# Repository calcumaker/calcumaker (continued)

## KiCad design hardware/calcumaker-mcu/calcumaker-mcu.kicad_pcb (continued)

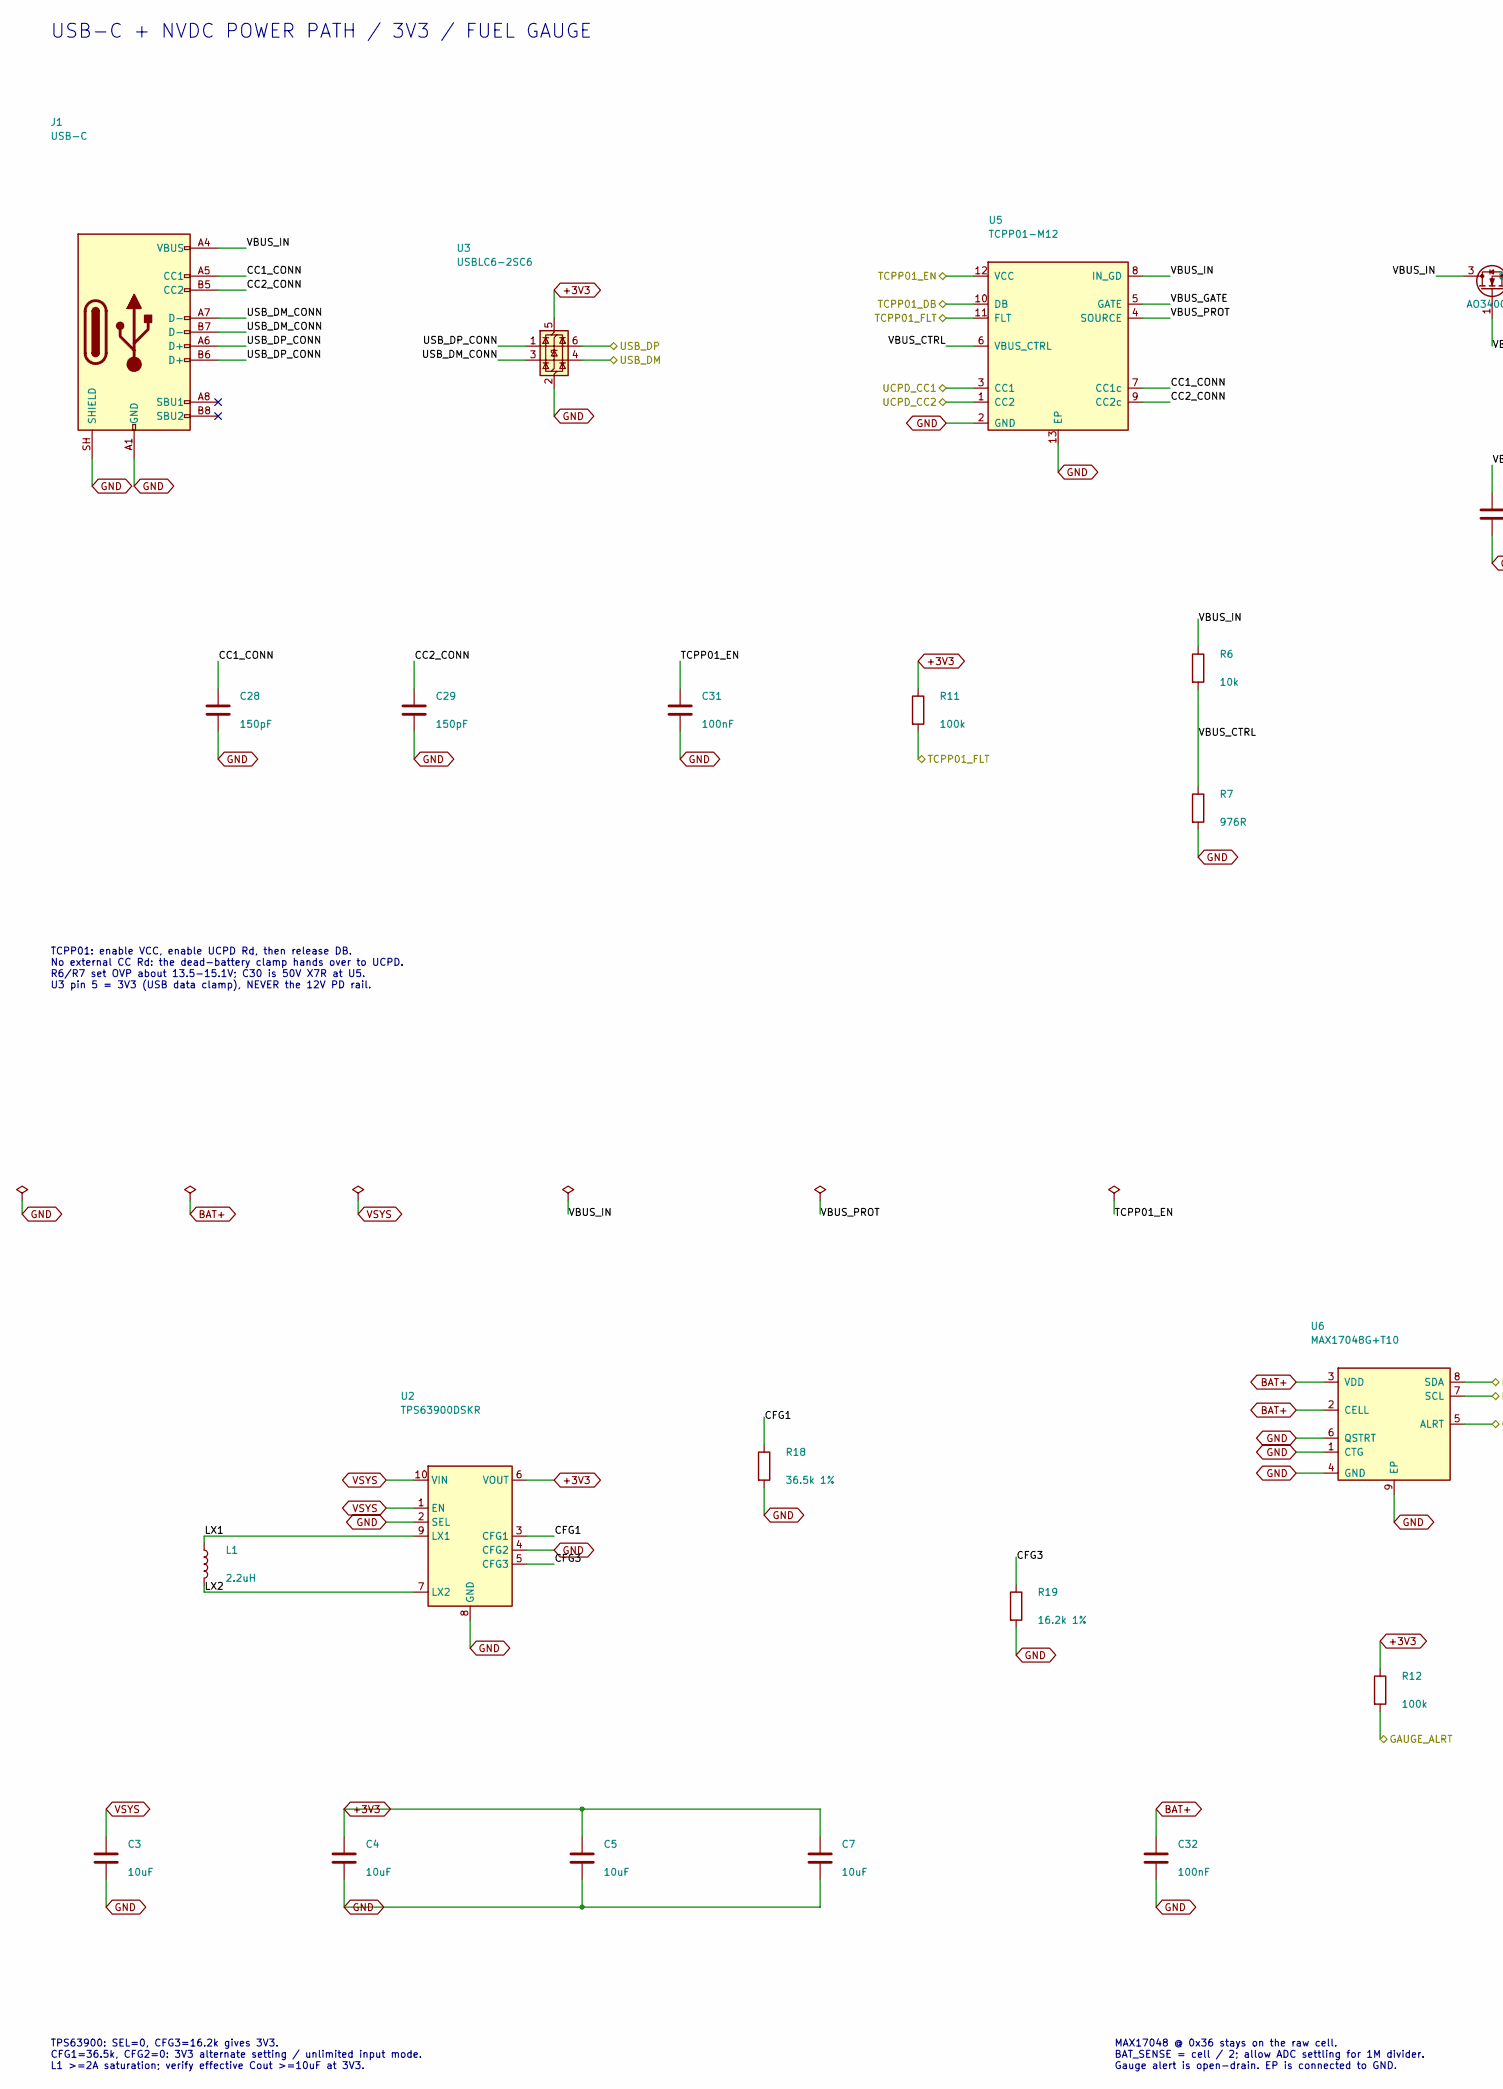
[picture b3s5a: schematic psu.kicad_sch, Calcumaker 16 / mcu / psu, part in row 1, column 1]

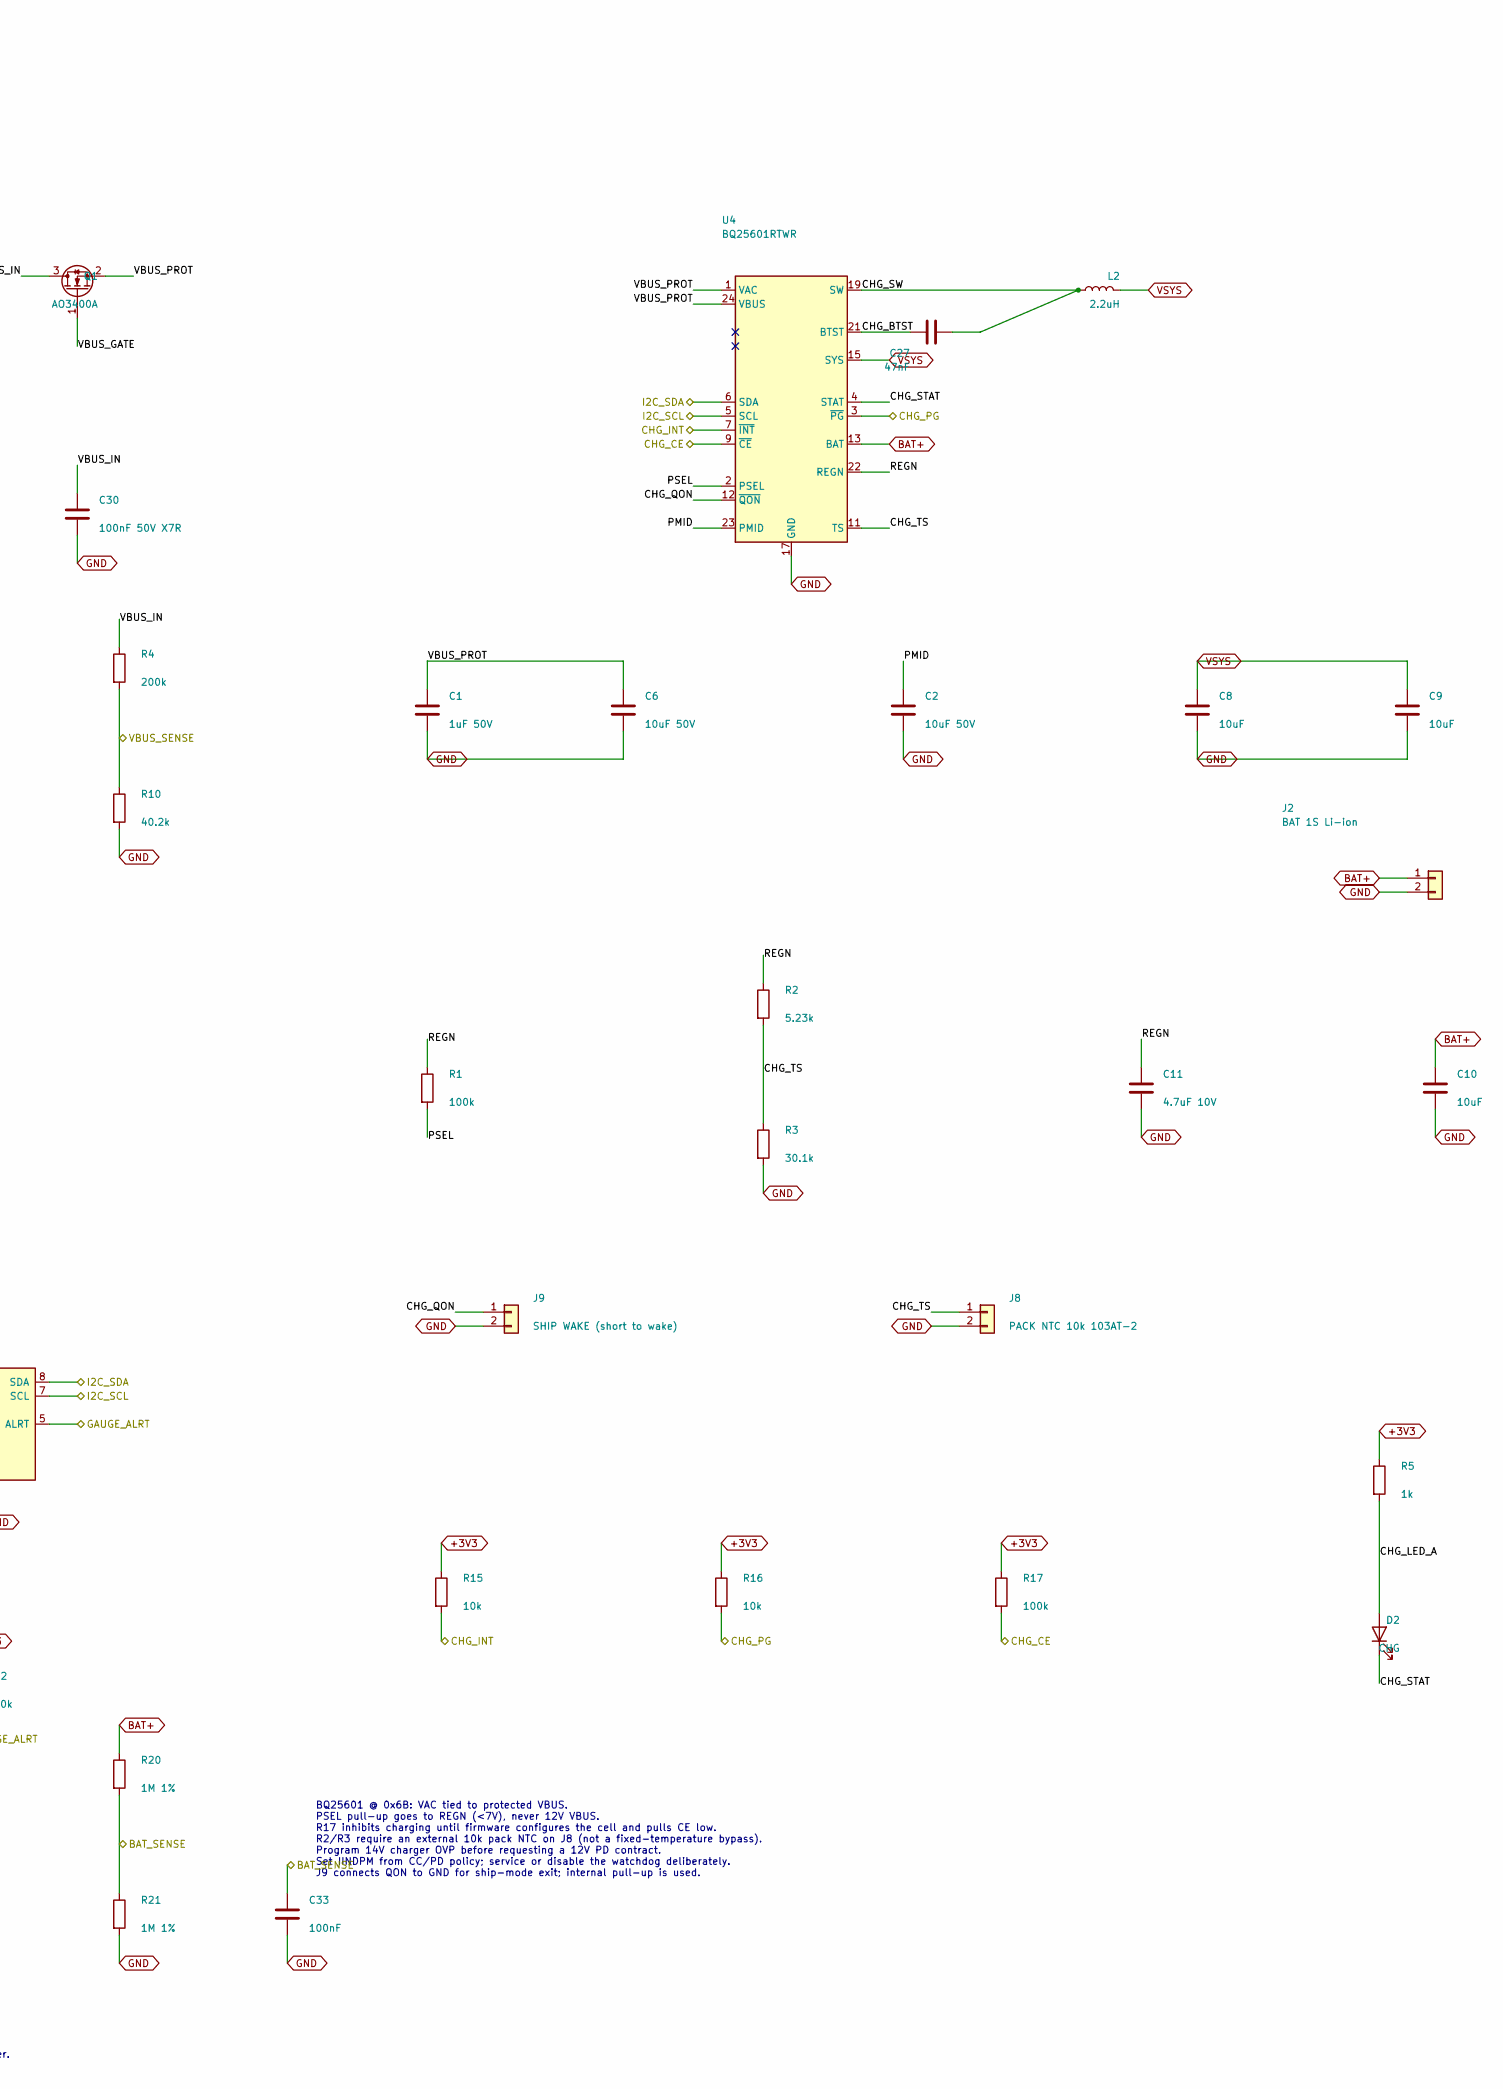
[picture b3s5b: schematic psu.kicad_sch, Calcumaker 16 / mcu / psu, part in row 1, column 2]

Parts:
C1: 1uF 50V; C_0603_1608Metric; MPN CL10A105KB8NNNC; LCSC C15849
C2, C6: 10uF 50V; C_0805_2012Metric; MPN GRM21BR61H106KE43L; LCSC C440198
C3, C4, C5, C7, C8, C9, C10: 10uF; C_0603_1608Metric
C11: 4.7uF 10V; C_0603_1608Metric
C27: 47nF; C_0402_1005Metric
C28, C29: 150pF; C_0402_1005Metric
C30: 100nF 50V X7R; C_0603_1608Metric; MPN CC0603KRX7R9BB104; LCSC C14663
C31, C32: 100nF; C_0402_1005Metric; LCSC C1525
C33: 100nF; C_0402_1005Metric
D2: CHG; LED_0402_1005Metric; LCSC C130719
J1: USB-C; USB_C_Receptacle_GCT_USB4105-xx-A_16P_TopMnt_Horizontal; MPN USB-TYPE-C-019; LCSC C2927039
J2: BAT 1S Li-ion; JST_PH_S2B-PH-K_1x02_P2.00mm_Horizontal; MPN S2B-PH-K-S; LCSC C173752
J8: PACK NTC 10k 103AT-2; JST_PH_S2B-PH-K_1x02_P2.00mm_Horizontal
J9: SHIP WAKE (short to wake); PinHeader_1x02_P2.54mm_Vertical
L1: 2.2uH; L_0805_2012Metric
L2: 2.2uH; L_Changjiang_FNR4020S
Q1: AO3400A; SOT-23; MPN AO3400A; LCSC C20917
R1, R11, R12: 100k; R_0402_1005Metric; LCSC C25741
R2: 5.23k; R_0402_1005Metric
R3: 30.1k; R_0402_1005Metric
R4: 200k; R_0402_1005Metric
R5: 1k; R_0402_1005Metric; LCSC C11702
R6: 10k; R_0402_1005Metric; LCSC C25744
R7: 976R; R_0402_1005Metric
R10: 40.2k; R_0402_1005Metric
R15, R16: 10k; R_0402_1005Metric
R17: 100k; R_0402_1005Metric
R18: 36.5k 1%; R_0402_1005Metric
R19: 16.2k 1%; R_0402_1005Metric
R20, R21: 1M 1%; R_0402_1005Metric
U2: TPS63900DSKR; WSON-10-1EP_2.5x2.5mm_P0.5mm_EP1.2x2mm; MPN TPS63900DSKR; LCSC C1518762
U3: USBLC6-2SC6; SOT-23-6; MPN USBLC6-2SC6; LCSC C2687116
U4: BQ25601RTWR; Texas_RTW_WQFN-24-1EP_4x4mm_P0.5mm_EP2.7x2.7mm_ThermalVias; MPN BQ25601RTWR; LCSC C468236
U5: TCPP01-M12; QFN-12-1EP_3x3mm_P0.5mm_EP1.45x1.45mm_ThermalVias; MPN TCPP01-M12; LCSC C1121848
U6: MAX17048G+T10; TDFN-8-1EP_2x2mm_P0.5mm_EP0.8x1.2mm; MPN MAX17048G+T10; LCSC C2682616

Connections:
+3V3: C4.1, C5.1, C7.1, R5.1, R11.1, R12.1, R15.1, R16.1, R17.1, U2.6 (VOUT), U3.5 (VBUS); also elsewhere on the board
/BAT_SENSE: C33.1, R20.2, R21.1; also elsewhere on the board
/CHG_CE: R17.2, U4.9 (~CE); also elsewhere on the board
/CHG_INT: R15.2, U4.7 (~INT); also elsewhere on the board
/CHG_PG: R16.2, U4.3 (~PG); also elsewhere on the board
/GAUGE_ALRT: R12.2, U6.5 (ALRT); also elsewhere on the board
/I2C_SCL: U4.5 (SCL), U6.7 (SCL); also elsewhere on the board
/I2C_SDA: U4.6 (SDA), U6.8 (SDA); also elsewhere on the board
/PSU/CC1_CONN: C28.1, J1.A5 (CC1), U5.7 (CC1c)
/PSU/CC2_CONN: C29.1, J1.B5 (CC2), U5.9 (CC2c)
/PSU/CFG1: R18.1, U2.3 (CFG1)
/PSU/CFG3: R19.1, U2.5 (CFG3)
/PSU/CHG_BTST: C27.1, U4.21 (BTST)
/PSU/CHG_LED_A: D2.2 (A), R5.2
/PSU/CHG_QON: J9.1, U4.12 (~QON)
/PSU/CHG_STAT: D2.1 (K), U4.4 (STAT)
/PSU/CHG_SW: C27.2, L2.1, U4.19 (SW), U4.20 (SW)
/PSU/CHG_TS: J8.1, R2.2, R3.1, U4.11 (TS)
/PSU/LX1: L1.1, U2.9 (LX1)
/PSU/LX2: L1.2, U2.7 (LX2)
/PSU/PMID: C2.1, U4.23 (PMID)
/PSU/PSEL: R1.2, U4.2 (PSEL)
/PSU/REGN: C11.1, R1.1, R2.1, U4.22 (REGN)
/PSU/USB_DM_CONN: J1.A7 (D-), J1.B7 (D-), U3.3 (I/O2)
/PSU/USB_DP_CONN: J1.A6 (D+), J1.B6 (D+), U3.1 (I/O1)
/PSU/VBUS_CTRL: R6.2, R7.1, U5.6 (VBUS_CTRL)
/PSU/VBUS_GATE: Q1.1 (G), U5.5 (GATE)
/PSU/VBUS_IN: C30.1, J1.A4 (VBUS), J1.A9 (VBUS), J1.B4 (VBUS), J1.B9 (VBUS), Q1.3 (D), R4.1, R6.1, U5.8 (IN_GD)
/PSU/VBUS_PROT: C1.1, C6.1, Q1.2 (S), U4.1 (VAC), U4.24 (VBUS), U5.4 (SOURCE)
/TCPP01_DB: U5.10 (DB); also elsewhere on the board
/TCPP01_EN: C31.1, U5.12 (VCC); also elsewhere on the board
/TCPP01_FLT: R11.2, U5.11 (FLT); also elsewhere on the board
/UCPD_CC1: U5.3 (CC1); also elsewhere on the board
/UCPD_CC2: U5.1 (CC2); also elsewhere on the board
/USB_DM: U3.4 (I/O2); also elsewhere on the board
/USB_DP: U3.6 (I/O1); also elsewhere on the board
/VBUS_SENSE: R4.2, R10.1; also elsewhere on the board
BAT+: C10.1, C32.1, J2.1, R20.1, U4.13 (BAT), U4.14 (BAT), U6.2 (CELL), U6.3 (VDD)
GND: C1.2, C2.2, C3.2, C4.2, C5.2, C6.2, C7.2, C8.2, C9.2, C10.2, C11.2, C28.2, C29.2, C30.2, C31.2, C32.2, C33.2, J1.A1 (GND), J1.A12 (GND), J1.B1 (GND), J1.B12 (GND), J1.SH (SHIELD), J2.2, J8.2, J9.2, R3.2, R7.2, R10.2, R18.2, R19.2, R21.2, U2.2 (SEL), U2.4 (CFG2), U2.8 (GND), U2.11 (GND), U3.2 (GND), U4.17 (GND), U4.18 (GND), U4.25 (GND), U5.2 (GND), U5.13 (EP), U6.1 (CTG), U6.4 (GND), U6.6 (QSTRT), U6.9 (EP); also elsewhere on the board
VSYS: C3.1, C8.1, C9.1, L2.2, U2.1 (EN), U2.10 (VIN), U4.15 (SYS), U4.16 (SYS); also elsewhere on the board

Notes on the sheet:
BQ25601 @ 0x6B: VAC tied to protected VBUS. PSEL pull-up goes to REGN (<7V), never 12V VBUS. R17 inhibits charging until firmware configures the cell and pulls CE low. R2/R3 require an external 10k pack NTC on J8 (not a fixed-temperature bypass). Program 14V charger OVP before requesting a 12V PD c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
MAX17048 @ 0x36 stays on the raw cell. BAT_SENSE = cell / 2; allow ADC settling for 1M divider. Gauge alert is open-drain. EP is connected to GND.
TPS63900: SEL=0, CFG3=16.2k gives 3V3. CFG1=36.5k, CFG2=0: 3V3 alternate setting / unlimited input mode. L1 >=2A saturation; verify effective Cout >=10uF at 3V3.
TCPP01: enable VCC, enable UCPD Rd, then release DB. No external CC Rd: the dead-battery clamp hands over to UCPD. R6/R7 set OVP about 13.5-15.1V; C30 is 50V X7R at U5. U3 pin 5 = 3V3 (USB data clamp), NEVER the 12V PD rail.
USB-C + NVDC POWER PATH / 3V3 / FUEL GAUGE

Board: 2 copper layers, 75 parts (0 on the bottom side), 65 nets, no tracks yet.

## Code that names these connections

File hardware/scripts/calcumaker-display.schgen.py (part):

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DIGIT_FP  = "Display_7Segment:7SegmentLED_LTS6760_LTS6780"  # 0.56" single-digit land

# UNIFIED display-module connector pinout (MUST match mcu J3 + the RGB-matrix J1)
UNIFIED_PINS = {1: "VSYS", 2: "VSYS", 3: "GND", 4: "GND", 5: "+3V3",
                6: "SPI_SCLK", 7: "SPI_MOSI", 8: "SPI_CS",
                9: "DISP_IRQ", 10: "DISP_NRST", 11: "DISP_BOOT", 12: "GND"}
RLCSC = {"10k": "C25744", "100k": "C25741", "732k": "", "4.7k": "C25900"}
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             comments=["Programmer's/technical arbitrary-precision RPN calculator",
                       "Display board: multi-channel 7-seg RPN stack + drivers + interconnect (DRAFT)"])

# segment (FJ5161AH pin name) -> TM1640 SEG line. a..g,dp = SEG1..SEG8 (matches
# firmware seg7 bit order: bit0=a .. bit7=dp -> TM1640 SEG1..SEG8).
SEGMAP = {"A": "SEG1", "B": "SEG2", "C": "SEG3", "D": "SEG4",
          "E": "SEG5", "F": "SEG6", "G": "SEG7", "DP": "SEG8"}
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        wiring += K.net_pin(U, f"GRID{n}", f"GRID{n}")               # right, per digit
    wiring += K.net_pin(U, "VDD", "+5V", kind="glabel")
    wiring += K.net_pin(U, "VSS", "GND", kind="glabel")
    wiring += K.net_pin(U, "SCLK", "DISP_CLK", kind="glabel")         # shared clock
    wiring += K.net_pin(U, "DIN", "DIN", kind="hlabel", shape="input")  # per-row -> sheet pin

    # --- 16 digits (8 across x 2 down) --------------------------------------
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        "  GRID1..16          -  one per digit  (GRID k -> digit k cathode)",
        "  VDD  -> +5V              VSS  -> GND",
        "  SCLK -> DISP_CLK (global net, shared by all 3 rows)",
        "  DIN  -> hierarchical pin (Row1<-DIN1, Row2<-DIN2, Row3<-DIN3 @ root)",
        "",
        "Runs at +5V (VDD + LED) from the MCU-board EN-gated 5V boost.",
        "Digit->GRID is 1:1 sequential; firmware seg7/App is the source of truth.",
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    for pin, net in UNIFIED_PINS.items():
        wiring += K.net_pin(J1, pin, net, kind="glabel")
    C7 = dict(_C("10uF", C0603), x=g(48), y=g(28))
    wiring += K.net_pin(C7, 1, "VSYS", kind="glabel")     # bulk on the incoming VSYS
    wiring += K.net_pin(C7, 2, "GND", kind="glabel")
    comps = [(J1, [(path, "J1")]), (C7, [(path, "C7")])]
    note = (20.0, 120.0, K.note_block(
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        "0.5mm 12-pos FFC to the MCU board. SAME connector + pinout as the RGB-",
        "matrix board's J1 and mcu J3 -> the display modules are INTERCHANGEABLE.",
        "",
        K.pin_table([(1, "VSYS"), (2, "VSYS"), (3, "GND"), (4, "GND"), (5, "+3V3"),
                     (6, "SPI_SCLK"), (7, "SPI_MOSI"), (8, "SPI_CS"), (9, "DISP_IRQ"),
                     (10, "DISP_NRST (G0 NRST)"), (11, "DISP_BOOT (G0 BOOT0)"),
                     (12, "GND")]),
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    w += K.net_pin(U4, 4, "+3V3", kind="glabel")          # VDD
    w += K.net_pin(U4, 5, "GND", kind="glabel")           # VSS
    w += K.net_pin(U4, 33, "GND", kind="glabel")          # VSS/EP
    w += K.net_pin(U4, 6, "DISP_NRST", kind="glabel")     # PF2/NRST
    w += K.net_pin(U4, 7, "DISP_IRQ", kind="glabel")      # PA0 -> IRQ out
    w += K.net_pin(U4, 11, "SPI_CS", kind="glabel")       # PA4  SPI1 NSS
    w += K.net_pin(U4, 12, "SPI_SCLK", kind="glabel")     # PA5  SPI1 SCK
    w += K.net_pin(U4, 14, "SPI_MOSI", kind="glabel")     # PA7  SPI1 MOSI
    w += K.net_pin(U4, 24, "SWDIO", kind="label")         # PA13
    w += K.net_pin(U4, 25, "SWCLK", kind="label")         # PA14
    w += K.net_pin(U4, 15, "CLK_3V3", kind="glabel")      # PB0 -> shifter -> DISP_CLK
    w += K.net_pin(U4, 16, "DIN1_3V3", kind="glabel")     # PB1 -> DIN1
    w += K.net_pin(U4, 17, "DIN2_3V3", kind="glabel")     # PB2 -> DIN2
    w += K.net_pin(U4, 27, "DIN3_3V3", kind="glabel")     # PB3 -> DIN3
    w += K.net_pin(U4, 30, "OLED_SCL", kind="glabel")     # PB6 I2C1 SCL
    w += K.net_pin(U4, 31, "OLED_SDA", kind="glabel")     # PB7 I2C1 SDA

    # decoupling + reset
    for i, (ref, val, fp) in enumerate([("C8", "100nF", C0402), ("C9", "100nF", C0402),
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        w += K.net_pin(c, 1, "+3V3", kind="glabel")
        w += K.net_pin(c, 2, "GND", kind="glabel")
    C12 = one(dict(C("C12", "100nF"), x=g(30), y=g(66)), "C12")       # NRST cap
    w += K.net_pin(C12, 1, "DISP_NRST", kind="glabel")
    w += K.net_pin(C12, 2, "GND", kind="glabel")
    R1 = one(dict(R("R1", "10k"), x=g(36), y=g(66)), "R1")            # BOOT0/DISP_BOOT pulldown
    w += K.net_pin(R1, 1, "DISP_BOOT", kind="glabel")
    w += K.net_pin(R1, 2, "GND", kind="glabel")

    # SWD Tag-Connect
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                  value="SWD TC2030-NL", fp=SWD_FP, x=g(60), y=g(44)), "J3")
    w += K.net_pin(J3, 1, "+3V3", kind="glabel")
    w += K.net_pin(J3, 2, "SWDIO", kind="label")
    w += K.net_pin(J3, 3, "DISP_NRST", kind="glabel")
    w += K.net_pin(J3, 4, "SWCLK", kind="label")
    w += K.net_pin(J3, 5, "GND", kind="glabel")

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        "MODULE MCU (WIRED)  -  U4 STM32G031K8U6 (C432207, UFQFPN-32)",
        "SPI-slave frame receiver -> renders 'display intent' to the 3 TM1640s.",
        "POWER  VDD(4)->+3V3 (C8/C9 100nF + C11 4.7uF); VSS(5,33)->GND.",
        "RESET  NRST=PF2(6)->DISP_NRST + C12 100nF.  BOOT0: R1 10k on DISP_BOOT;",
        "       route to the G031 BOOT0/option-byte at layout (UART-boot entry).",
        "LINK   SPI1 PA5/PA7/PA4 <- SPI_SCLK/MOSI/CS;  PA0 -> DISP_IRQ.",
        "DRIVE  PB0-3 -> CLK_3V3 + DIN1/2/3_3V3 (3V3) -> DispPower shifters -> 5V",
        "       to the TM1640s (Row1-3). CLOCK internal HSI.",
        "OLED   PB6/PB7 = I2C1 SCL/SDA -> AuxDisplay J2.  PROG  J3 SWD Tag-Connect."))
    return dict(uuid=MCU_SH, file="disp_mcu.kicad_sch", page="8",
                title="Module MCU (STM32G031K8U6, SPI-slave) — wired",
                comps=comps, wiring=w, notes=[note], _dir=PROJ_DIR)
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    U5 = one(dict(lib_id="Converter_DCDC:TPS61022", value="TPS61022RWUR", fp=BOOST_FP,
                  lcsc="C915088", mpn="TPS61022RWUR", mfr="Texas Instruments",
                  x=g(30), y=g(44)), "U5")
    w += K.net_pin(U5, 7, "VSYS", kind="glabel")          # VIN
    w += K.net_pin(U5, 2, "SW", kind="label")             # SW node (to L1)
    w += K.net_pin(U5, 3, "+5V", kind="glabel")           # VOUT
    w += K.net_pin(U5, 4, "FB", kind="label")             # feedback
    w += K.net_pin(U5, 5, "VSYS", kind="glabel")          # EN -> always on (gate off = a GPIO later)
    w += K.net_pin(U5, 6, "GND", kind="glabel")           # MODE -> GND (forced PWM)
    w += K.net_pin(U5, 1, "GND", kind="glabel")           # GND
    L1 = one(dict(lib_id="Device:L", value="1uH", fp=L2016, lcsc="C5832342",
                  mpn="FTC201610S1R0MBCA", mfr="Sunlord", x=g(18), y=g(40)), "L1")
    w += K.net_pin(L1, 1, "VSYS", kind="glabel")
    w += K.net_pin(L1, 2, "SW", kind="label")
    C13 = one(dict(C("C13", "10uF", C0603), x=g(10), y=g(50)), "C13")   # Cin
    w += K.net_pin(C13, 1, "VSYS", kind="glabel")
    w += K.net_pin(C13, 2, "GND", kind="glabel")
    for i, ref in enumerate(("C14", "C15")):                            # Cout 2x22uF
        c = one(dict(C(ref, "22uF", C0603), x=g(46 + i * 5), y=g(50)), ref)
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        "LOCAL 5V RAIL + LEVEL SHIFT (WIRED)  -  moved off the MCU board.",
        "5V BOOST  U5 TPS61022 (C915088): VIN<-VSYS, L1 1uH (VSYS->SW), Cin C13",
        "  10uF, Cout C14/C15 2x22uF; FB R2 732k / R3 100k -> +5V (Vref 0.6V).",
        "  EN->VSYS (always on; tie to a G031 GPIO to gate off in deep sleep).",
        "SHIFT  U6-U9 74HCT1G125 @ +5V (VIH=2V accepts 3V3): A <- G031 CLK/DIN1/2/3",
        "  (3V3), Y -> DISP_CLK + DIN1/2/3 (5V) to the TM1640s. /OE=GND; C16-19",
        "  decouple. *** VERIFY the 74HCT1G125GW package (SOT-353 vs the SOT-23-5",
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# ============================ root sheet ====================================
def build_root_strings():
    # 3 reused row instances + interconnect + aux, with per-row DIN routed to
    # DIN1/2/3 global labels.
    sym = ""
    wiring = ""
    for i, (uuid, name) in enumerate([(R1, "Row1"), (R2, "Row2"), (R3, "Row3")]):
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        "Calcumaker 16 — Display (MULTI-CHANNEL). Row1/2/3 are three instances "
        "of ONE reusable sheet (display_row.kicad_sch). Shared bus is carried on "
        "global nets +5V / GND / DISP_CLK; each row's serial data DIN is a "
        "hierarchical pin fed by DIN1/DIN2/DIN3 from the interconnect. Top row "
        "(Row3 / U3 / DS33-48) is optional -> 2- or 3-row build.", 20.0, 105.0)
    pro_sheets = [[R1, "Row1"], [R2, "Row2"], [R3, "Row3"],
                  [IC, "Interconnect"], [AX, "AuxDisplay"],
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
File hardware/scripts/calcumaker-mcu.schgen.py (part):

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        dict(ref="J3", lib_id="Connector_Generic:Conn_01x12", value="TO DISPLAY (unified SPI FFC)",
             fp="Connector_FFC-FPC:Hirose_FH12-12S-0.5SH_1x12-1MP_P0.50mm_Horizontal",
             lcsc="C262661", mpn="AFC01-S12FCA-00", mfr="JUSHUO"),
        # VSYS outlet -> the RGB-matrix module's LED inlet (its own 2-pin JST).
        dict(ref="J7", lib_id="Connector_Generic:Conn_01x02", value="VSYS -> matrix LED pwr",
             fp="Connector_JST:JST_PH_S2B-PH-K_1x02_P2.00mm_Horizontal",
             lcsc="C173752", mpn="S2B-PH-K-S", mfr="JST"),
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        "",
        "PIN MAP  (verified vs the ST CubeMX pin DB for LQFP-64)",
        "  OCTOSPI1 -> U7      OCTOSPIM Port 1; IO0-3 forced, 1 pin each",
        "    CLK  PB10 AF10 p29      IO0  PB1  AF10 p27",
        "    NCS  PA4  AF3  p20      IO1  PB0  AF10 p26",
        "                            IO2  PA7  AF10 p23",
        "                            IO3  PA6  AF10 p22",
        "  SPI1 -> display J3  (PA6/PA7 are QSPI now; the FFC has no MISO)",
        "    SCK  PA5  AF5  p21      MOSI PB5  AF5  p57",
        "    CS   PA8       p41      (plain GPIO -- MOVED off PA15, now UCPD1_CC1)",
        "  UCPD1  -> USB-C CC   CC1 PA15 p50 / CC2 PB15 p63   (dedicated analog,",
        "                       NO AF alt -- this is why SPI1 CS had to move.",
        "                       Rd is INTERNAL: no 5.1k parts.  DBCC1/DBCC2 unused,",
        "                       so PB5 stays SPI1 MOSI.)",
        "  USART2 -> keyboard   TX PA2 p16 / RX PA3 p17   AF7",
        "  I2C1   -> keyboard + CHARGER   SCL PB6 p58 / SDA PB7 p59 AF4",
        "                       (shared bus; BQ25601 = 0x6B, no addr clash)",
        "",
        "ON THIS SHEET  (Clock / Programming / DisplayIF merged in here)",
        "  SWD   PA13/PA14 (+ PB3 SWO)      -> J4 Tag-Connect (+ NRST)",
        "  LSE   PC14/PC15 OSC32            -> Y1 + C24/C25",
        "  DISP  SPI1 + DISP_IRQ/NRST/BOOT  -> J3 FFC ; J7 VSYS outlet",
        "",
        "OFF-SHEET",
        "  USB   PA11/PA12                     -> PSU ESD (U3)",
        "  CC    PA15/PB15 (UCPD1)             -> PSU ESD (U5) -> USB-C CC1/CC2",
        "  CHG   I2C1 + CHG_INT/CHG_PG/CHG_CE  -> PSU charger U4",
        "  KBD   I2C1+USART2+KB_IRQ/NRST/BOOT0 -> KeyboardIF J5/J6",
        "  QSPI  OCTOSPI1 CLK/NCS/IO0-3        -> QSPIFlash U7",
        "",
        "KB_IRQ must land on a WKUP pin (keypress wake from Stop) -- still open.",
        "",
        "---- J3  UNIFIED DISPLAY-MODULE FFC  (was the DisplayIF sheet) --------",
        "0.5mm 12-pos FFC (AFC01-S12FCA-00, C262661). SAME pinout on BOTH display",
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        "7-seg / RP2040 on the matrix) is the SPI slave + renders locally; 5V and",
        "any level-shifting are generated ON the module now.",
        "",
        K.pin_table([(1, "VSYS"), (2, "VSYS"), (3, "GND"), (4, "GND"), (5, "+3V3"),
                     (6, "SPI_SCLK"), (7, "SPI_MOSI"), (8, "SPI_CS"), (9, "DISP_IRQ"),
                     (10, "DISP_NRST"), (11, "DISP_BOOT"), (12, "GND")]),
        "",
        "J7 = 2-pin JST-PH VSYS outlet -> the RGB-matrix module's LED inlet (J2):",
        "the matrix pulls amps for 2304 LEDs, so its LED current takes this direct",
        "lead, NOT the signal FFC (the 7-seg module boosts from VSYS on the FFC).",
        "CABLE (non-BOM): GCT FFC05-TIN 05-12-A-<len>-A-4-06-4-T (DigiKey; len TBD).",
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        "---- J4  SWD PROGRAMMING  (was the Programming sheet) ----------------",
        "Tag-Connect TC2030-NL (no-legs pogo pad). Bare land, no part mounted.",
        "",
        K.pin_table([(1, "+3V3 (VTref)"), (2, "SWDIO (PA13)"), (3, "NRST"),
                     (4, "SWCLK (PA14)"), (5, "GND"), (6, "SWO (PB3, opt)")], cols=1),
        "",
        "---- Y1  LSE 32.768 kHz  (was the Clock sheet) -----------------------",
        "Q13FC13500004, LCSC C32346.  Y1.1 -> OSC32_IN (PC14)",
        "                             Y1.2 -> OSC32_OUT (PC15)",
        "  C24 / C25 -> LSE load caps to GND   (12pF shown)",
        "Load caps: CL match = 2*(CL - Cstray); trim with the RTC SMOOTHCALIB.",
        "Drives the RTC for sleep timing.")))
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        #      and closes the CC switches, handing CC over to UCPD.  This is what
        #      closes the old "dead-battery Rd" risk (was Open Question 8).
        #   2. CC SHORT-TO-VBUS OVP (6.0V clamp).  A defective cable/source putting
        #      20V on CC would otherwise destroy PA15/PB15 -- a USBLC6 is an ESD
        #      clamp (ns transients), NOT sustained-overvoltage protection.
        # Plus IEC61000-4-2 level 4 ESD on CC, and adjustable VBUS OVP via an
        # external N-FET it gate-drives.  Sourced by the user: 300 pcs on JLCPCB.
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        dict(ref="U3", lib_id="Power_Protection:USBLC6-2SC6", value="USBLC6-2SC6",
             fp=SOT236, lcsc="C2687116", mpn="USBLC6-2SC6", mfr="STMicroelectronics"),
        # -- USB-C CC -> TCPP01 (connector side CC1c/CC2c, 22V tolerant) -> MCU side
        # CC1/CC2 -> the U575's UCPD1 (CC1=PA15, CC2=PB15; dedicated analog pins, NO
        # AF alternative -- which is why the display SPI1 CS moved off PA15 to PA8).
        # There are NO 5.1k Rd resistors: in the run state UCPD generates Rd
        # INTERNALLY (CcPull::Sink).  It is either/or -- an external 5.1k in parallel
        # with the internal Rd = 2.55k, and the source would misread us as an audio
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        # (UCPD_SR.TYPEC_VSTATE_CC: LOWEST=detached LOW=500mA HIGH=1.5A HIGHEST=3.0A);
        # fw reads it and writes IINDPM over I2C.  UCPD also carries the BMC PHY, so
        # real USB-PD later is FIRMWARE-ONLY -- no respin.
        #   DB/ is a plain 3V3 GPIO (NOT the UCPD DBCC1/DBCC2 pins) -- so PB5 stays
        #   SPI1 MOSI and DBCC1/DBCC2 remain unused.  Datasheet 6.4.
        R("R11", "100k"),                                # FLT/ pull-up (open-drain)
        # VBUS OVP threshold: VBUS_CTRL trips at Vovp = 1.20 (min) / 1.25 (typ) /
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        "    !! BELOW a legal 12V source -> nuisance trips on a good charger.",
        "  VBUS SENSE:  J1 VBUS -> R4 200k -> VBUS_SENSE (ADC) -> R10 40.2k -> GND",
        "    (not needed at 5V; a PD policy engine REQUIRES it -> keeps PD fw-only)",
        "  CC:  J1 CC1 -> CC1c(7) ... CC1(3) -> PA15 (UCPD1_CC1)   [+C28 150pF]",
        "       J1 CC2 -> CC2c(9) ... CC2(1) -> PB15 (UCPD1_CC2)   [+C29 150pF]",
        "    connector side is 22V tolerant; U5 clamps CC at 6.0V -> a CC short to",
        "    VBUS can no longer destroy the MCU's CC pins.",
        "  CONTROL:  VCC(12) <- TCPP01_EN GPIO (+C31 100nF)  -- powering VCC from a",
        "    GPIO gives NULL quiescent current when unplugged (datasheet 5).",
        "            DB/(10)  <- TCPP01_DB  GPIO   (plain 3V3 GPIO, NOT UCPD DBCC!",
        "                                          so PB5 stays SPI1 MOSI)",
        "            FLT/(11) -> TCPP01_FLT GPIO   open-drain, + R11 100k pull-up",
        "            GND(2) + EP(13) -> GND   <-- EP IS A REAL GROUND RETURN, not just",
        "                                         thermal.  It is a VISIBLE pin: WIRE IT.",
        "",
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# wake line (keyboard -> MCU) and reset/boot for reflashing the keyboard MCU.
# J5 = Hirose DF40 2x6 (12-pin) 0.4mm RECEPTACLE (DF40B-12DS, LCSC C3641147); the
# keyboard board carries the mating header (DF40C-12DP C6224952). Grown 10 -> 12
# pins to carry VSYS + a dedicated GND up to the keyboard for its per-key RGB
# lighting. (DF40C-12DS isn't LCSC-stocked, so the receptacle is DF40B-12DS --
# same 1.5mm stack: on DF40 the receptacle SUFFIX sets the height [none=1.5mm,
# (2.0)=2.0mm], not the B/C letter, and the DF40C plug is the common header.)
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        "PLACED, not wired.  The keyboard end (MainIF) mirrors both connectors.",
        "",
        "J5 DF40 (12-pin):",
        K.pin_table([(1, "+3V3"), (2, "GND"), (3, "SDA"), (4, "SCL"), (5, "UART_TX"),
                     (6, "UART_RX"), (7, "KB_IRQ"), (8, "KB_NRST"), (9, "KB_BOOT0"),
                     (10, "GND"), (11, "VSYS"), (12, "GND")]),
        "J6 FFC (16-pin: VSYS x2, GND x3 for LED current + 2 spare):",
        K.pin_table([(1, "+3V3"), (2, "GND"), (3, "SDA"), (4, "SCL"), (5, "UART_TX"),
                     (6, "UART_RX"), (7, "KB_IRQ"), (8, "KB_NRST"), (9, "KB_BOOT0"),
                     (10, "GND"), (11, "VSYS"), (12, "VSYS"), (13, "GND"), (14, "GND"),
                     (15, "NC"), (16, "NC")]),
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        "QSPI FLASH  -  U7  W25Q32JVSSIQ  (LCSC C179173)",
        "4MB (32Mbit) quad-SPI NOR, SOIC-8, 2.7-3.6V, on the STM32U575 OCTOSPI1.",
        "",
        K.pin_table([("1", "CS#         <-  NCS     PA4   AF3    p20  (+R9 10k)"),
                     ("6", "CLK         <-  CLK     PB10  AF10   p29"),
                     ("5", "IO0 / DI    <-> IO0     PB1   AF10   p27"),
                     ("2", "IO1 / DO    <-> IO1     PB0   AF10   p26"),
                     ("3", "IO2 / WP#   <-> IO2     PA7   AF10   p23"),
                     ("7", "IO3 / HOLD# <-> IO3     PA6   AF10   p22"),
                     ("8", "VCC = +3V3   (C26 100nF at pin 8)"),
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
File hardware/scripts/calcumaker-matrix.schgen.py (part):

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**data chain** (768 LEDs) driven by one RP2040 PIO line via the quad level shifter.

**Power.** LED current (amps at brightness) does NOT cross the signal FFC: the
board takes a dedicated 2-pin VSYS inlet (J2) from the MCU-board PSU, gated by a
high-side load switch (LED_EN off in sleep). Firmware MUST cap total brightness.

This is DATA; the engine is scripts/kschgen.py. Verify each lib_id/footprint
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CLCSC = {"100nF": "C1525", "1uF": "C29266", "10uF": "C15850", "22uF": "C45783", "15pF": ""}

# ---- UNIFIED display-module connector pinout (MUST match mcu J3 + 7-seg J1) --
UNIFIED_PINS = {1: "VSYS", 2: "VSYS", 3: "GND", 4: "GND", 5: "+3V3",
                6: "SPI_SCLK", 7: "SPI_MOSI", 8: "SPI_CS",
                9: "DISP_IRQ", 10: "DISP_NRST", 11: "DISP_BOOT", 12: "GND"}

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                   x=g(8 + cc * 6), y=g(10 + rr * 6))
        # ref: global cluster index gc = r*12 + c ; 64 LEDs per cluster
        comps.append((led, pr(lambda r, c, jj=j: f"D{(r * NCLUST + c) * PER_CLUSTER + jj}")))
        wiring += K.net_pin(led, "VDD", "VLED", kind="glabel")
        wiring += K.net_pin(led, "VSS", "GND", kind="glabel")
        if j == 1:
            wiring += K.net_pin(led, "DIN", "DIN", kind="hlabel", shape="input")
        else:
            wiring += K.net_pin(led, "DIN", f"CN{j}", kind="label")
        if j == PER_CLUSTER:
            wiring += K.net_pin(led, "DOUT", "DOUT", kind="hlabel", shape="output")
        else:
            wiring += K.net_pin(led, "DOUT", f"CN{j + 1}", kind="label")

    note = (g(4), g(66), K.note_block(
        "REUSABLE 8x8 LED CLUSTER  (leaf of the nested design)",
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        "Refs D1..D2304: cluster gc = r*12+c  ->  D(64*gc+1) .. D(64*gc+64).",
        "",
        "64x XL-1010RGBC-2812B-S (C51900942, 1x1mm WS2812/SK6812, 3.5-5.5V):",
        "  DIN -> LED1 -> ... -> LED64 -> DOUT  (serpentine; DIN/DOUT = hier pins,",
        "         chained cluster-to-cluster in led_row, row-to-row at the root)",
        "  VDD -> VLED (gated LED rail);  VSS -> GND",
        "",
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        # DOUT side: cluster 11 = row DOUT (hier); else RC{c+1}
        wiring += K.w_wire(cx + cw, opy, cx + cw + g(2), opy)
        if c == NCLUST - 1:
            wiring += K.w_hlabel("DOUT", cx + cw + g(2), opy, 0, shape="output")
        else:
            wiring += K.w_label(f"RC{c + 1}", cx + cw + g(2), opy, 0)
    note = K.text_note(K.note_block(
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    for n, net in [(52, "QSPI_SCLK"), (53, "QSPI_SD0"), (55, "QSPI_SD1"),
                   (54, "QSPI_SD2"), (51, "QSPI_SD3"), (56, "QSPI_CS")]:
        w += K.net_pin(U1, n, net, kind="glabel")
    w += K.net_pin(U1, 47, "USB_DP", kind="glabel")
    w += K.net_pin(U1, 46, "USB_DM", kind="glabel")
    w += K.net_pin(U1, 26, "DISP_NRST", kind="glabel")    # RUN <- reset from U575
    w += K.net_pin(U1, 24, "SWCLK", kind="glabel")
    w += K.net_pin(U1, 25, "SWDIO", kind="glabel")
    # peripheral GPIOs (by pin number)
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    w += K.net_pin(U3, "VBUS", "VBUS", kind="glabel")
    w += K.net_pin(U3, "GND", "GND", kind="glabel")
    R2 = one(dict(R("R2", "27"), x=g(40), y=g(72)), "R2")
    w += K.net_pin(R2, 1, "USB_DP", kind="glabel")
    w += K.net_pin(R2, 2, "USB_DP_C", kind="label")
    R3 = one(dict(R("R3", "27"), x=g(40), y=g(78)), "R3")
    w += K.net_pin(R3, 1, "USB_DM", kind="glabel")
    w += K.net_pin(R3, 2, "USB_DM_C", kind="label")
    J4 = one(dict(lib_id="Connector:USB_C_Receptacle_USB2.0_16P", value="USB-C (BOOTSEL)",
                  fp=USBC_FP, lcsc="C2927039", mpn="USB-TYPE-C-019", mfr="GCT",
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    J2 = one(dict(lib_id="Connector_Generic:Conn_01x02", value="VSYS IN (LED pwr)",
                  fp=JST2_FP, lcsc="C173752", mpn="S2B-PH-K-S", mfr="JST",
                  x=g(8), y=g(12)), "J2")
    w += K.net_pin(J2, 1, "VSYS", kind="glabel")
    w += K.net_pin(J2, 2, "GND", kind="glabel")

    # High-side P-FET: VSYS -> VLED, gate = QG (R5 pull-up to VSYS = OFF default)
    Q1 = one(dict(lib_id="Transistor_FET:Q_PMOS_GSD", value="AO3401A", fp=SOT23,
                  lcsc="C15127", mpn="AO3401A", mfr="AOS", x=g(26), y=g(16)), "Q1")
    w += K.net_pin(Q1, "S", "VSYS", kind="glabel")
    w += K.net_pin(Q1, "D", "VLED", kind="glabel")
    w += K.net_pin(Q1, "G", "QG", kind="label")
    R5 = one(dict(R("R5", "100k"), x=g(26), y=g(6)), "R5")
    w += K.net_pin(R5, 1, "VSYS", kind="glabel")
    w += K.net_pin(R5, 2, "QG", kind="label")
    # N-FET pulls QG low when LED_EN is high (R7 pulldown = OFF at boot/sleep)
    Q2 = one(dict(lib_id="Transistor_FET:Q_NMOS_GSD", value="2N7002", fp=SOT23,
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    w += K.net_pin(Q2, "S", "GND", kind="glabel")
    w += K.net_pin(Q2, "G", "QEN", kind="label")
    R6 = one(dict(R("R6", "10k"), x=g(40), y=g(26)), "R6")
    w += K.net_pin(R6, 1, "LED_EN", kind="glabel")
    w += K.net_pin(R6, 2, "QEN", kind="label")
    R7 = one(dict(R("R7", "100k"), x=g(48), y=g(26)), "R7")
    w += K.net_pin(R7, 1, "QEN", kind="label")
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    for i, (ref, val, fp) in enumerate([("C13", "22uF", C0603), ("C14", "22uF", C0603),
                                        ("C15", "100nF", C0402)]):
        c = one(dict(C(ref, val, fp), x=g(56 + i * 5), y=g(12)), ref)
        w += K.net_pin(c, 1, "VLED", kind="glabel")
        w += K.net_pin(c, 2, "GND", kind="glabel")

    # 3x single-gate shifter: A <- LED_DATAk (RP2040 3V3), Y -> CHk_DATA (VLED);
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        U = one(dict(lib_id="74xGxx:74LVC1G125", value="74LVC1G125", fp=SOT235,
                     lcsc="C23654", mpn="SN74LVC1G125DBVR", mfr="Texas Instruments",
                     x=g(10 + (k - 1) * 18), y=g(44)), f"U{3 + k}")
        w += K.net_pin(U, 5, "VLED", kind="glabel")            # VCC
        w += K.net_pin(U, 3, "GND", kind="glabel")             # GND
        w += K.net_pin(U, 1, "GND", kind="glabel")             # /OE low = enabled
        w += K.net_pin(U, 2, f"LED_DATA{k}", kind="glabel")    # A  <- RP2040 (3V3)
        w += K.net_pin(U, 4, f"CH{k}_DATA", kind="glabel")     # Y  -> chain k
        cc = one(dict(C(f"C{15 + k}", "100nF"), x=g(10 + (k - 1) * 18), y=g(54)), f"C{15 + k}")
        w += K.net_pin(cc, 1, "VLED", kind="glabel")
        w += K.net_pin(cc, 2, "GND", kind="glabel")

    note = (g(4), g(64), K.note_block(
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        "no display-specific lines). Distinct pinout from the old CLK/DIN display",
        "FFC and from the 16-pin keyboard link (can't cross-plug).",
        "",
        K.pin_table([(1, "VSYS"), (2, "VSYS"), (3, "GND"), (4, "GND"), (5, "+3V3"),
                     (6, "SPI_SCLK"), (7, "SPI_MOSI"), (8, "SPI_CS"), (9, "DISP_IRQ"),
                     (10, "DISP_NRST (RP2040 RUN)"), (11, "DISP_BOOT (RP2040 BOOTSEL)"),
                     (12, "GND")]),
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        "the unified connector -- the main MCU sends OLED content inside the SPI",
        "display-intent stream. Add 4.7k pull-ups (DNP with the module).",
        "",
        K.pin_table([(1, "VCC <- +3V3"), (2, "GND"), (3, "SCL <- OLED_SCL"),
                     (4, "SDA <- OLED_SDA")], cols=1),
        "",
        "Shows full-precision X / error text / SETUP; the matrix stays primary."))
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        "Calcumaker 16 - RGB Matrix (NESTED MULTI-CHANNEL: cluster -> row -> board).",
        "Row1..Row3 = 3 instances of led_row.kicad_sch; each led_row = 12 instances",
        "of led_cluster.kicad_sch (8x8 = 64x XL-1010). Grid 96x24 = 2304 px. Shared",
        "globals VLED (gated) / GND; DIN/DOUT are hier pins chained cluster->cluster",
        "then row->row: CHr_DATA -> Row_r -> CHr_END. RP2040 PIO drives 3 data lines",
        "via RGBPower's quad shifter; RGBPower gates VLED off in sleep. Wire the",
        "one-off sheets in eeschema. Same unified SPI connector as the 7-seg board."),
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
